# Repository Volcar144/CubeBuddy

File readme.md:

\# CubeBuddy
This is a PCB / Hardware project designed as the week 1 submission for hack-club half-life challenge.

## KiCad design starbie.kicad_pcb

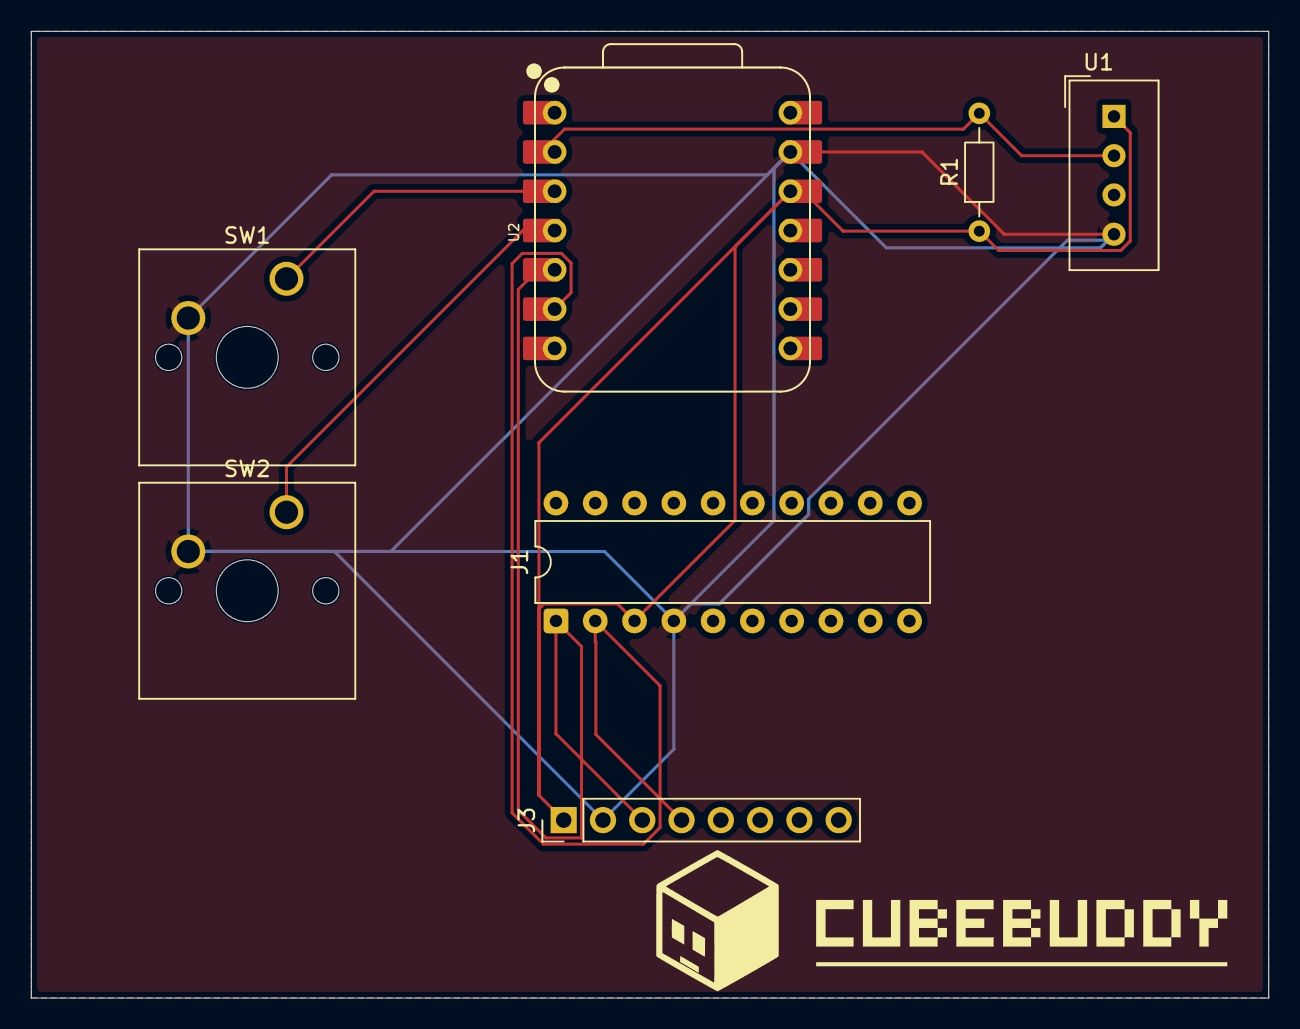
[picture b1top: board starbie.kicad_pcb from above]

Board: 2 copper layers, 80.0 x 62.5 mm, 7 parts (0 on the bottom side), 7 nets.

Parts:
J1: Conn_01x04_Pin; DIP-20_W7.62mm
J3: Conn_01x08_Pin; PinHeader_1x08_P2.54mm_Vertical
R1: 10k; R_Axial_DIN0204_L3.6mm_D1.6mm_P7.62mm_Horizontal
SW1, SW2: SW_Push; SW_Cherry_MX_1.00u_PCB
U1: DHT11; Aosong_DHT11_5.5x12.0_P2.54mm
U2: XIAO-ESP32-C3-SMD; XIAO-ESP32-C6-DIP

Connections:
+3.3V: J1.3, J3.1, R1.1, U1.1 (VDD), U2.12 (3V3_OUT)
/DHT11 DATA: R1.2, U1.2 (DATA), U2.2 (D1)
/GPIO2: SW1.1, U2.3 (D2)
/GPIO3: SW2.1, U2.4 (D3)
/SCL: J1.1, J3.3, U2.5 (D4)
/SDA: J1.2, J3.4, U2.6 (D5)
GND: J1.4, J3.2, SW1.2, SW2.2, U1.4 (GND), U2.13 (GND)
